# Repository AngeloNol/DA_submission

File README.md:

# UNLV CpE 301 Embedded System Design

# OverView
* Study of the microcontrollers and its application to a broad range of engineering problems.
Study of architecture, instruction set, interfaces, etc. Study of Assembly and C
programming for microcontrollers. Use of simulation and emulation. Study of
microcontroller interface with sensors, actuators, motors, peripheral devices and
communication. 
* implemented design assignment and midterm project using a ATMEGA 328P in Microchip Studio

# Components
Software:
* Mircochip Studio
* KiCad

Hardware:
* ATMEGA 328P Xplained Mini
* Ardunio Multi-function Shield
* Arduino Prototype Shield
* USB Logic Analyzer
* LCD
* Stepper Motor
* DC Motor
* Servo Motor
* Ultrasonic Sensor
* MPU-6050

# Design Assignments
* DA1 - Write, simulate, and demonstrate using Microchip Studio 7 an assembly code for the AVR
ATMEGA328P/PB microcontroller that performs the following functions:
    1. Store a 16-bit number 0x1234 at SRAM location 0x402. Verify the number stored in the
    location.
    2. Store a 16-bit number in 0x5678 at SRAM location 0x410. Verify the number stored in the
    location.
    3. Sum the above two numbers and store the result in EEPROM starting location. Verify the
    number stored in the location.
    4. Store 10 16-bit numbers starting from 0x0910 at Program Memory location using code and
    retrieve them to 0x500 SRAM location using X pointer. Sum the 10 numbers and store the
    sum in SRAM location 0x406.

* DA2 - The goal of the assignment is use GPIO, delays, and Interrupts:
    1. Design a delay subroutine to generate a delay of 0.25 sec.
    2. Connect a switch to PORTC.3 (active high - turn on the pull up transistor) to poll for an event to
    turn on the led at PORTB.2 for 1.25 sec after the event.
    3. Connect a switch to INT0 (PD2 pin) (active high - turn on the pull up transistor) and using an
    interrupt mechanism turn on the led at PORTB.1 for 0.5 sec after the event.
    4. All of the above constitutes for a single task. Verify the delay using simulation and logic analyzer.

 * DA4 - The goal of the assignment is to develop the above code to do the following:
    1. Write an AVR C program to measure the distance using the HC-SR04 ultrasonic module.
    2. Use the Timer Capture function to determine the ECHO capture pulse.
    3. Display the results every 1 sec on the serial terminal.

 * DA5 - The goal of the assignment is to develop the above code to do the following:
    1. Write an AVR C program to control the speed of the DC Motor using a potentiometer connected to PC0.
    2. Write an AVR C program to control the speed of the Stepper Motor using a potentiometer connected to PC0. Use a timer in CTC mode to control the delay.
    3. Write an AVR C program to control the position of the Servo Motor using a potentiometer connected to PC0. When pot value is 0 the servo is at position 0 deg. and when pot value is max (approx. 5V) 
       the servo is at position 180 deg.

 * DA6 - The goal of the assignment is to develop the above code to do the following:
    1. Interface the provided ICM-20948 9-DOF IMU Sensor to the ATmega328pb using the I2C
    interface. Using the earlier developed code for UART, display the accelerometer, gyro, and magnetometer data to the UART Terminal.
    2. Apply Simple averaging algorithm to smooth the values to the accelerometer, gyro, and magnetometer data. Plot the above nine values as graphs.
    3. Apply Complementary to the accelerometer, gyro, and magnetometer data to determine the roll, pitch, and yaw of the sensor orientation. Plot the above three values as graphs.

# MidTerm
* Midterm 1 : UART Interface
   - Program the UART Module to interact with the ATmega328pb:
        1. On transmitting the following keys from the host terminal, the following actions will be performed:
        1. On-reboot or ‘h’ key – help screen (list all keys and functionalities)
        2. ‘o’ - turns ON LED at PB5, ‘O’ turns OFF the LED at PB5.
        3. ‘p’ - Blink (on-off) the LED PB3. Choose your own period. Only use timer mode. ‘P’ turns off
        the LED PB3/stops this operation.
        4. ‘f’ - fade the intensity of LED PB1. Choose your own frequency and step resolution. ‘F’ turns
        off the LED PB1/stops this operation.
        5. ‘b’ – reads the status of the switch at PC1. Display the status in terminal. Exit this function
        when there is change of switch status.
        6. Use UART RX interrupt for all of the above operations.

* Midterm 2 : US + Servo Motor
      1. Mount the HC-SR04 Ultrasonic sensor on to the servo motor using the mounting plate/horn. Scan
    the servo motor from 0 – 180 deg. Collect the US distance/raw value continuously during the scan.
    The resolution of scan has to be less that 2.5 deg.
    2. Display your results as a two dimensional, 0 -180 deg distance graph. Update your scan after every
    scan range. 

# KiCad PCB Design
* Design a Atmega 328P with compnents like LED, potentiometer, two push buttons, ICM-20948 sensor

# Student Info
* Student Name: Angelo Nolasco
* Student Email: Nolasco@unlv.nevada.edu
* youtube link DAs: https://www.youtube.com/playlist?list=PLQKv7ukC_Zva5RjXT9Pd358gahEjTsdrr 
* youtube link MidTerm: https://www.youtube.com/playlist?list=PLQKv7ukC_ZvZvBtWoRn7U3fXBtwM975KZ

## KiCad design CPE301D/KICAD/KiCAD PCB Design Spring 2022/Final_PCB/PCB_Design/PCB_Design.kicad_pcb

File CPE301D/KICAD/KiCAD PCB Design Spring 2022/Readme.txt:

Student Name: Angelo Nolasco

Student #: 5005497011

Student Email: Nolasco@unlv.nevada.edu

Primary Github address: angelon3121@gmail.com

Symbol/FootPrint
8-1437565-1 : button
3362P-1-103LF : potentiometer
ICM-20948
LTST-C191EKT : red led
RC0603JR-071KL :resistor

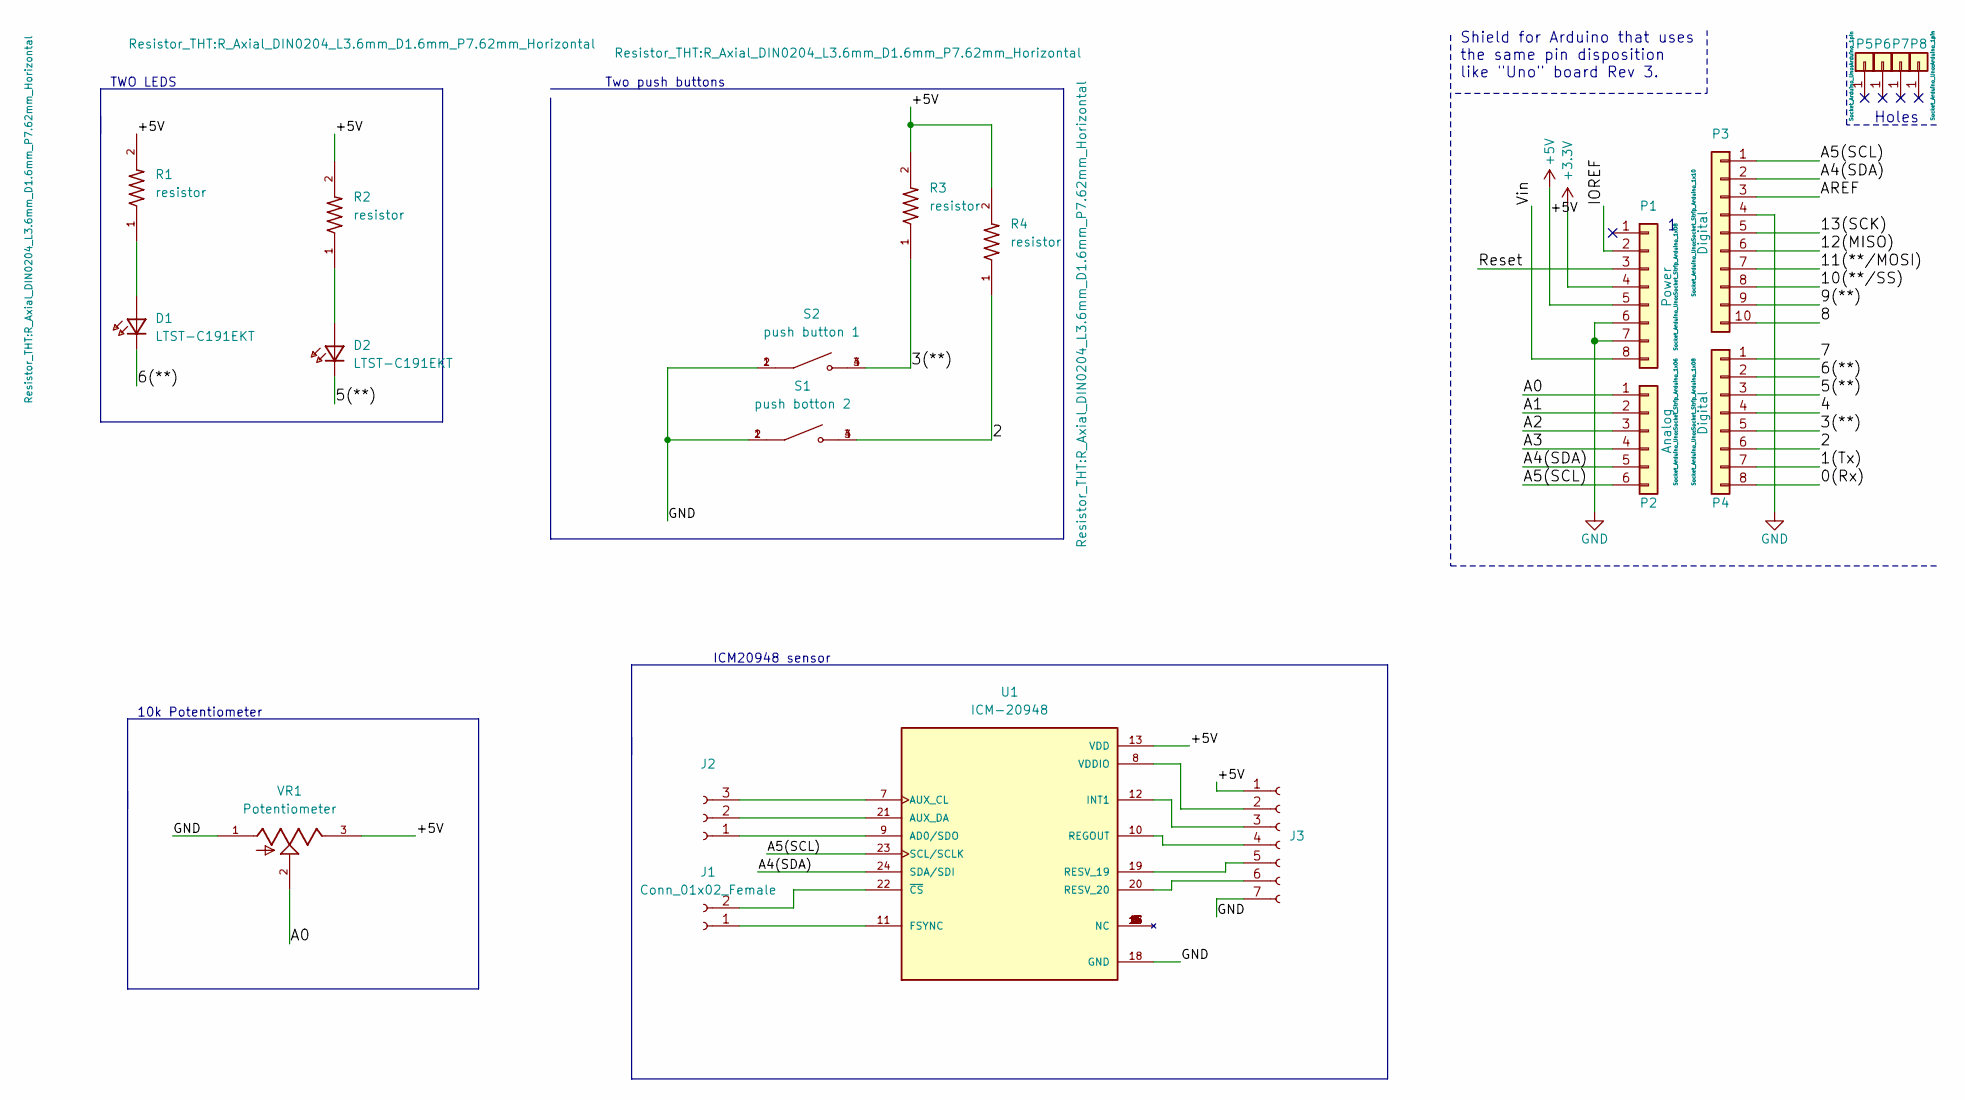
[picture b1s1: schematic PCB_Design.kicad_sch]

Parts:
D1, D2: LTST-C191EKT; 0603
J1: Conn_01x02_Female
J2, J3: (no value)
P1: Power; Socket_Strip_Arduino_1x08
P2: Analog; Socket_Strip_Arduino_1x06
P3: Digital; Socket_Strip_Arduino_1x10
P4: Digital; Socket_Strip_Arduino_1x08
P5, P6, P7, P8: CONN_01X01; Arduino_1pin
R1, R2, R3, R4: resistor; R_Axial_DIN0204_L3.6mm_D1.6mm_P7.62mm_Horizontal
S1: push botton 2; SW_8-1437565-1
S2: push button 1; SW_8-1437565-1
U1: ICM-20948; QFN40P300X300X105-24N; PARTREV 1.3
VR1: Potentiometer; TRIM_3362P-1-103LF; PARTREV 08/26/10

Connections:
+3V3: P1.4
+5V: J3.1, P1.5, R1.2, R2.2, R3.2, R4.2, U1.13 (VDD), VR1.3
/0(Rx): P4.8
/1(Tx): P4.7
/2: P4.6, R4.1, S1.3, S1.4
/3(**): P4.5, R3.1, S2.3, S2.4
/4: P4.4
/5(**): D2.1, P4.3
/6(**): D1.1, P4.2
/7: P4.1
/8: P3.10
/9(**): P3.9
/10(**/SS): P3.8
/11(**/MOSI): P3.7
/12(MISO): P3.6
/13(SCK): P3.5
/A0: P2.1, VR1.2
/A1: P2.2
/A2: P2.3
/A3: P2.4
/A4(SDA): P2.5, P3.2, U1.24 (SDA/SDI)
/A5(SCL): P2.6, P3.1, U1.23 (SCL/SCLK)
/AREF: P3.3
/IOREF: P1.2
/Reset: P1.3
/Vin: P1.8
GND: J3.7, P1.6, P1.7, P3.4, S1.1, S1.2, S2.1, S2.2, U1.18 (GND), VR1.1
unnamed: D1.2, R1.1
unnamed: D2.2, R2.1
unnamed: J1.1, U1.11 (FSYNC)
unnamed: J1.2, U1.22 (~CS)
unnamed: J2.1, U1.9 (AD0/SDO)
unnamed: J2.2, U1.21 (AUX_DA)
unnamed: J2.3, U1.7 (AUX_CL)
unnamed: J3.2, U1.8 (VDDIO)
unnamed: J3.3, U1.12 (INT1)
unnamed: J3.4, U1.10 (REGOUT)
unnamed: J3.5, U1.19 (RESV_19)
unnamed: J3.6, U1.20 (RESV_20)

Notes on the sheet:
TWO LEDS
ICM20948 sensor
10k Potentiometer
Holes
Shield for Arduino that uses the same pin disposition like "Uno" board Rev 3.
Two push buttons

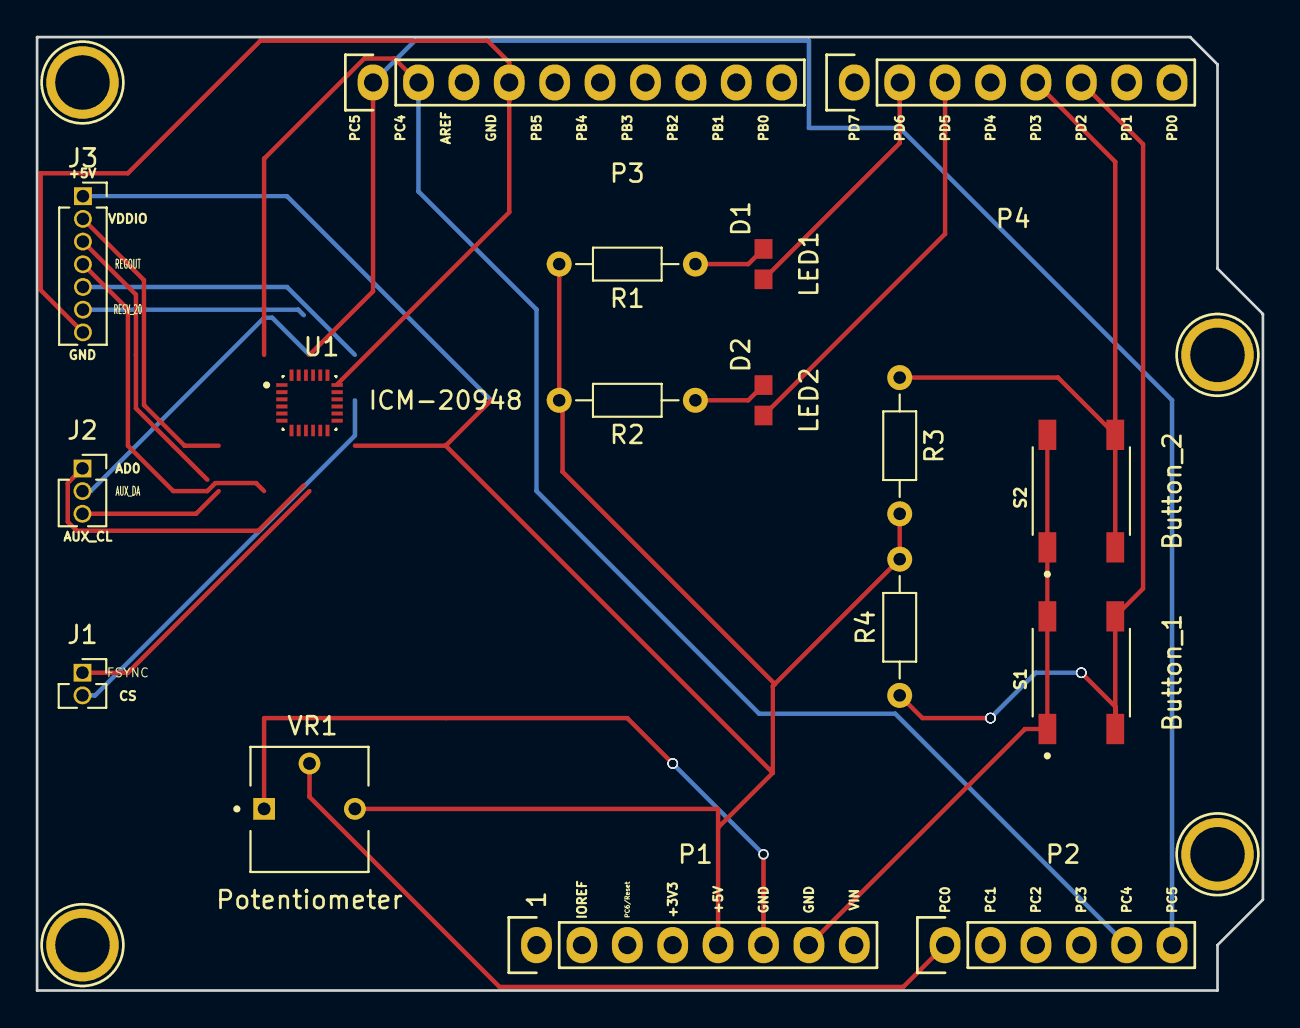
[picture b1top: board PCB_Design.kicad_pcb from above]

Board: 2 copper layers, 68.6 x 53.3 mm, 21 parts (0 on the bottom side), 21 nets.

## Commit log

2022-02-11 Design Assignment 1 upload
2022-02-11 Create DesignAssigment
2022-02-11 DA 1
2022-03-23 Midterm1
2022-05-10 PCB Design
